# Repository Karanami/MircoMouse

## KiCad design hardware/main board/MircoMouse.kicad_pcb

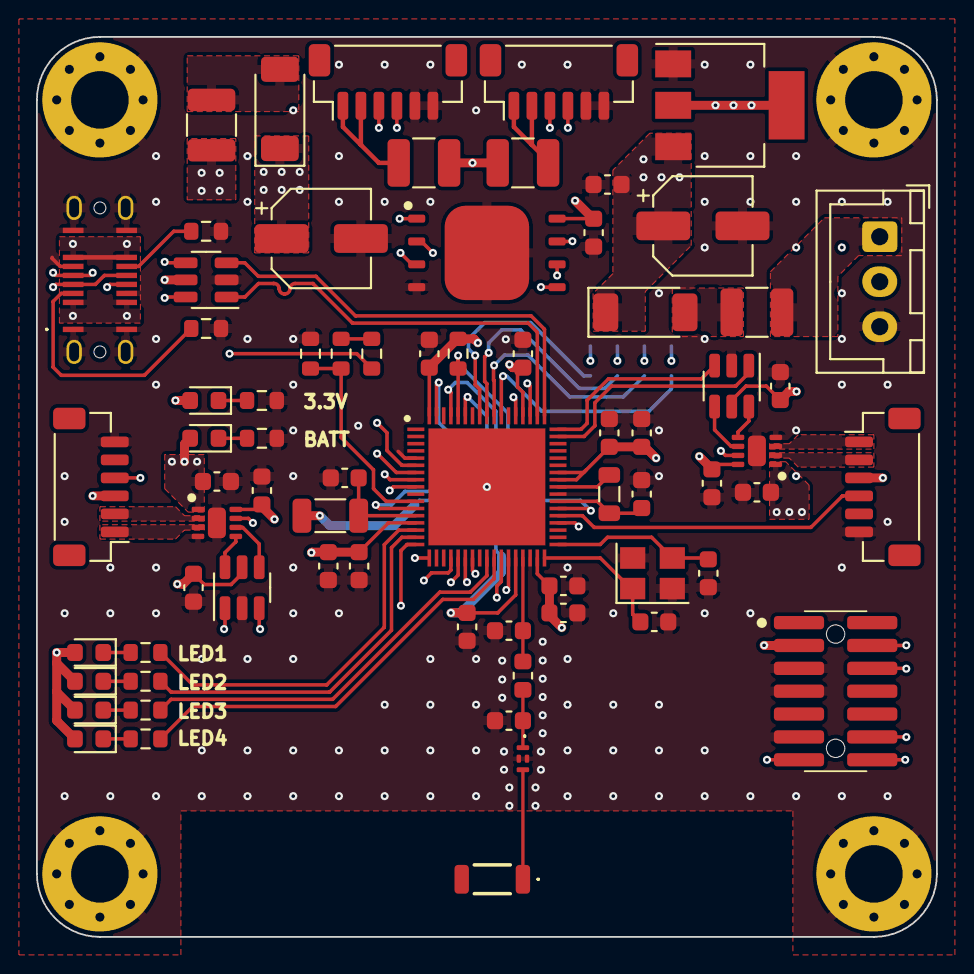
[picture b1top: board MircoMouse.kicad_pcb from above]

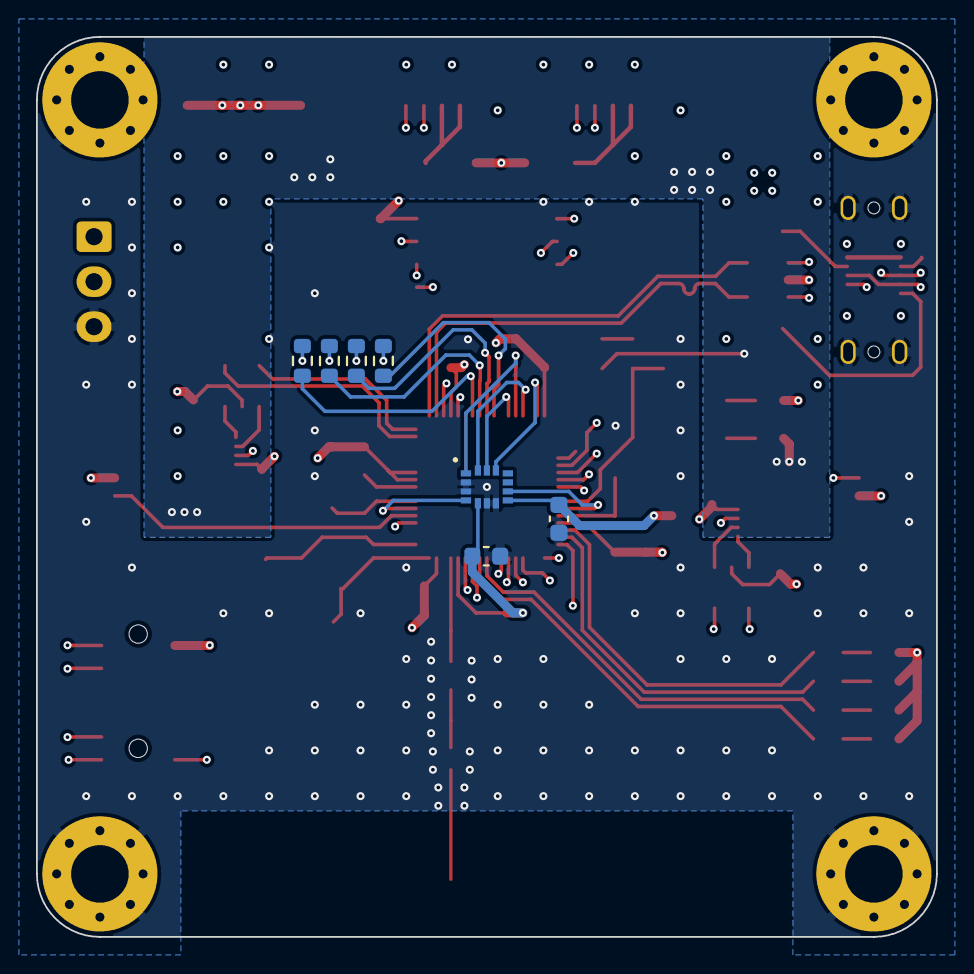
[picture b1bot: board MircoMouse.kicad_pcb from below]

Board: 8 copper layers, 50.0 x 50.0 mm, 81 parts (7 on the bottom side), 75 nets.

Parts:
ANT1: 74889302450
C1, C2: 30pF; C_0603_1608Metric
C3, C4, C5, C9, C11, C16, C19, C25, C26, C27, C28, C30, C31: 100nF; C_0603_1608Metric
C7: 10nF; C_0603_1608Metric
C8: 1uF; C_0603_1608Metric
C10: 100pF; C_0603_1608Metric
C13: 10uF; C_0603_1608Metric
C14, C15, C18, C24: 4.7uF; C_0603_1608Metric
C17, C29: 100uF; CP_Elec_5x4.5
C20: 0.3pF; C_0603_1608Metric
C21: 0.8pF; C_0603_1608Metric
D1, D3: RBS2LAM40CTR; D_SOD-128
D2, D4, D5, D6, D7, D8: LED_Small; LED_0603_1608Metric
F1, F2, F3, F4: 0.5A/16V; Fuse_1210_3225Metric
FL1: DLF162500LT-5028A1; DLF162500LT5028A1
H1, H2, H3, H4: MountingHole_Pad; MountingHole_3.2mm_M3_Pad_Via
IC1: STM32WB55RGV6; QFN40P800X800X100-69N-D
IC2, IC3: DRV8212PDSGR; SON50P200X200X80-9N
IC4: W25N01GVZEIG; SON127P800X600X80-9N-D
IC5: LSM6DSLTR
IC6, IC7: SN74LVC1G18DBVRG4; SOT-23-6
J1, J2, J5, J7: JST-SH 01x06; JST_SH_BM06B-SRSS-TB_1x06-1MP_P1.00mm_Vertical
J3: JST_XH_B3B; JST_XH_B3B-XH-A_1x03_P2.50mm_Vertical
J4: FTSH-107-01-L-DV-K-A; FTSH-107-XX-YYY-DV-K-A
J6: USB4145-03-0070-C; USB4145030070C
L1: 1mH; L_1206_3216Metric
L2: 74479774222; WE-PMI_080562
L3: 2.7nH; L_0603_1608Metric
R1: 1k; R_0603_1608Metric
R2, R3: 5.1k; R_0603_1608Metric
R4, R5, R6, R7, R8, R9, R10, R11, R12: 10k; R_0603_1608Metric
R13, R14, R15, R16: 100; R_0603_1608Metric
U1: LM1117MP-3.3; SOT-223-3_TabPin2
U2: USBLC6-2SC6; SOT-23-6
Y1: 8MHz; Crystal_SMD_3225-4Pin_3.2x2.5mm

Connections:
+3.3V: C3.2, C4.2, C5.2, C7.1, C8.1, C9.2, C10.2, C11.2, C15.1, C19.1, C25.1, C26.1, C27.2, C28.2, C30.1, C31.1, D2.2 (A), D4.2 (A), D5.2 (A), D6.2 (A), D7.2 (A), F3.2, F4.2, IC1.14 (VDDA), IC1.30 (VDD), IC1.33 (VDDRF), IC1.44 (VDDSMPS), IC1.45 (VDD), IC1.55 (VDDUSB), IC1.68 (VDD), IC2.8 (VCC), IC3.8 (VCC), IC4.8 (VCC), IC5.5 (VDDIO), IC5.8 (VDD), IC6.5 (VCC), IC7.5 (VCC), J1.3, J2.3, J4.3, L1.1, R1.1, U1.2 (VO)
+BATT: C16.1, C17.1, C18.1, C24.1, C29.1, D1.1 (K), D3.1 (K), D8.2 (A), IC2.1 (VM), IC3.1 (VM), R9.2, U1.3 (VI)
/ANT_IN: ANT1.1 (FEED), FL1.3 (OUT)
/CONN_D+: J6.A6 (D+), J6.B6 (D+), U2.6 (I/O1)
/CONN_D-: J6.A7 (D-), J6.B7 (D-), U2.4 (I/O2)
/FLT_IN: C21.2, FL1.1 (IN), L3.2
/M_LEFT_A: IC1.9 (PC0), J2.4
/M_LEFT_DIRECTION: IC1.24 (PA9), IC7.1
/M_LEFT_PWM: IC1.23 (PA8), IC7.3
/M_RIGHT_A: IC1.39 (PB1), J1.4
/M_RIGHT_DIRECTION: IC1.50 (PC6), IC6.1
/M_RIGHT_PWM: IC1.51 (PA10), IC6.3
/Motor Control Left/M+: IC2.3 (OUT2), J2.1
/Motor Control Left/M-: IC2.2 (OUT1), J2.2
/Motor Control Left/PWMF: IC2.6 (IN1), IC7.4
/Motor Control Left/PWMR: IC2.5 (IN2), IC7.6
/Motor Control Left/~SLEEP: IC1.38 (PB0), IC2.7 (~SLEEP), IC3.7 (~SLEEP)
/Motor Control Right/M+: IC3.3 (OUT2), J1.1
/Motor Control Right/M-: IC3.2 (OUT1), J1.2
/Motor Control Right/PWMF: IC3.6 (IN1), IC6.4
/Motor Control Right/PWMR: IC3.5 (IN2), IC6.6
/VBUS: F2.1, J6.A4 (VBUS), J6.A9 (VBUS), J6.B4 (VBUS), J6.B9 (VBUS), U2.5 (VBUS)
/VBUSFUSE: D3.2 (A), F2.2
/VCONN: F1.2, J3.1
/VFUSE: D1.2 (A), F1.1
/WALL_DETECT_B: IC1.61 (PD0), R15.2
/WALL_DETECT_F: IC1.59 (PC11), R13.2
/WALL_DETECT_L: IC1.60 (PC12), R16.2
/WALL_DETECT_R: IC1.58 (PC10), R14.2
/uC/ANT_OUT: C20.1, IC1.31 (RF1), L3.1
/uC/D+: IC1.53 (PA12), U2.1 (I/O1)
/uC/D-: IC1.52 (PA11), U2.3 (I/O2)
/uC/IMU_INT1: IC1.12 (PC3), IC5.9 (INT2)
/uC/IMU_INT2: IC1.40 (PE4), IC5.4 (INT1)
/uC/LED1: IC1.15 (PA0), R5.1
/uC/LED2: IC1.16 (PA1), R6.1
/uC/LED3: IC1.26 (PC5), R7.1
/uC/LED4: IC1.27 (PB2), R8.1
/uC/OSC_IN: C1.2, IC1.35 (OSC_IN), Y1.3
/uC/OSC_OUT: C2.1, IC1.34 (OSC_OUT), Y1.1
/uC/QSPI_CLK: IC1.18 (PA3), IC4.6 (CLK)
/uC/QSPI_IO0: IC1.7 (PB9), IC4.5 (DI(IO0))
/uC/QSPI_IO1: IC1.6 (PB8), IC4.2 (DO(IO1))
/uC/QSPI_IO2: IC1.22 (PA7), IC4.3 (~WP(IO2))
/uC/QSPI_IO3: IC1.21 (PA6), IC4.7 (~HOLD(IO3))
/uC/SPI_CLK: IC1.63 (PB3), IC5.13 (SCL)
/uC/SPI_MISO: IC1.64 (PB4), IC5.1 (SDO/SA0), R1.2
/uC/SPI_MOSI: IC1.65 (PB5), IC5.14 (SDI/SDA)
/uC/SWCLK: IC1.56 (PA14), J4.6
/uC/SWDIO: IC1.54 (PA13), J4.4
/uC/UART_RX: IC1.28 (PB10), J4.13
/uC/UART_TX: IC1.29 (PB11), J4.14
/uC/VBAT: IC1.11 (PC2), R10.2, R11.1
/uC/VFBSMPS: C14.1, IC1.41 (VFBSMPS), L2.2
/uC/VLXSMPS: IC1.43 (VLXSMPS), L2.1
/uC/VREF+: C13.2, IC1.13 (VREF+), L1.2
/uC/~QSPI_CS: IC1.17 (PA2), IC4.1 (~CS)
/uC/~RST: IC1.8 (~RST), J4.12
/uC/~SPI_IMU_CS: IC1.67 (PB7), IC5.12 (~CS)
GND: C1.1, C2.2, C3.1, C4.1, C5.1, C7.2, C8.2, C9.1, C10.1, C11.1, C13.1, C14.2, C15.2, C16.2, C17.2, C18.2, C19.2, C20.2, C21.1, C24.2, C25.2, C26.2, C27.1, C28.1, C29.2, C30.2, C31.2, FL1.2 (GND), FL1.4 (GND), H1.1, H2.1, H3.1, H4.1, IC1.5 (PH3-BOOT0), IC1.32 (VSSRF), IC1.42 (VSSSMPS), IC1.69 (EP), IC2.4 (GND), IC2.9 (EP), IC3.4 (GND), IC3.9 (EP), IC4.4 (GND), IC4.9 (EP), IC5.2 (SDX), IC5.3 (SCX), IC5.6 (GND), IC5.7 (GND), IC6.2 (GND), IC7.2 (GND), J1.6, J2.6, J3.3, J4.5, J4.7, J4.11, J5.5, J5.6, J6.A1 (GND), J6.A8 (SBU1), J6.A12 (GND), J6.B1 (GND), J6.B8 (SBU2), J6.B12 (GND), J6.MH (SHIELD), J7.5, J7.6, R2.2, R3.2, R4.1, R10.1, R12.1, U1.1 (GND), U2.2 (GND), Y1.2, Y1.4
unnamed: D2.1 (K), R4.2
unnamed: D4.1 (K), R5.2
unnamed: D5.1 (K), R6.2
unnamed: D6.1 (K), R7.2
unnamed: D7.1 (K), R8.2
unnamed: D8.1 (K), R12.2
unnamed: F3.1, J5.1, J5.2
unnamed: J5.3, R13.1
unnamed: J5.4, R14.1
unnamed: J6.A5 (CC1), R2.1
unnamed: J6.B5 (CC2), R3.1
unnamed: F4.1, J7.1, J7.2
unnamed: J7.3, R15.1
unnamed: J7.4, R16.1
unnamed: R9.1, R11.2

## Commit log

2024-10-30 init
2024-10-30 schematic changes to change it into a micro mouse
2024-12-30 done
2025-01-01 final
